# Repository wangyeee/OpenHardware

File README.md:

# OpenHardware
Collections of hardware design related to my drone project.

Brief description for each folders.

| Folder | Description | CAD software |
|---|---|---|
| CurrentMonitor | A simple [ACS758](https://www.allegromicro.com/en/Products/Current-Sensor-ICs/Fifty-To-Two-Hundred-Amp-Integrated-Conductor-Sensor-ICs/ACS758.aspx) breakout board | EAGLE |
| LoRaModem | A board with [Ra-02](http://wiki.ai-thinker.com/_media/lora/docs/c048ps01a1_ra-02_product_specification_v1.1.pdf) LoRa Module and [STM32](https://www.st.com/en/microcontrollers/stm32f103cb.html) MCU | KiCAD |
| OscillatorBreakout | A breakout board for oscillators, supporting three different oscillator packages | KiCAD |
| SimpleFC | Simple yet powerful flight controller for drones, capable of fully autonomous GPS navigation | KiCAD |
| SimpleFCv2 | Version 2 of SimpleFC, with reduced PCB size | KiCAD |
| SimpleFC_G | SimpleFCv2 with integrated GPS receiver | KiCAD |
| MultiRotorHub | A support board in multi-rotor which makes cable management easy | EAGLE |
| PowerModule  | 2s ~ 6s Li-Po BEC with current monitoring |EAGLE  |
| SerialBTBridge | A bridge board between RFM22B telemetry module and HC05 Bluetooth module | EAGLE |
| TinyFC | A tiny flight controller module, supporting board stacking for advanced features | KiCAD |
| ReflowOvenController | A controller board used to convert a commercial oven to PCB reflow oven. | KiCAD |
| AirSensor | A barometer and differential pressure sensor board with UAVCAN support. | KiCAD |
| DIYDummyLoad | A primitive DC dummy load with STM32F103. | EAGLE |
| TinyBEC | 2s ~ 3s / 2A Li-Po BEC, board size 23x18mm. | KiCAD |

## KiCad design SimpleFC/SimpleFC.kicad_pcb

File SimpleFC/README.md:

# SimpleFC
SimpleFC is a simple flight controller for drones.

## Features

- STM32F4 MCU with FPU
- 10DoF IMU (Gyro + Accel + Mag + Baro)
- Onboard UBlox GPS receiver
- DC-DC converter supports up to 6S Li-Po battery with power monitor.
- Two RC input channel with software controlled inverter for S.Bus receivers.
- 8 PWM outputs.
- Onboard TF card slot to record flight data.
- EEPROM to store parameters.
- CAN Bus support.
- USB and SWD available.

## Software
SimpleFC was originally designed to run modified version of [AutoQuad](http://autoquad.org/), the source can be found in my [fork](https://github.com/wangyeee/aq_flight_control) of AutoQuad. In additional, port for [PaparazziUAV](http://wiki.paparazziuav.org/wiki/Main_Page) is in progress. It will make SimpleFC support both fixwing and rotorcraft.

## STM32F4 resource usage
The following table summarizes usage of the MCU, details such as pinout and DMA allocation can be found in the [STM32CubeMX](https://www.st.com/en/development-tools/stm32cubemx.html) design file `SimpleFC.ioc`.

| MCU Peripheral | Usage |
|----|----|
| ADC1 | battery monitor and two analog inputs |
|CAN2 | CAN bus |
| I2C1 | [MAG3110](https://www.nxp.com/docs/en/data-sheet/MAG3110.pdf) magnetometer and EEPROM |
| SDIO | TF card slot |
| SPI1 | [ICM20689](http://www.invensense.com/wp-content/uploads/2017/08/ICM-20689-v2.2-002.pdf) gyroscope/accelerometer and [MS5611](https://www.te.com/commerce/DocumentDelivery/DDEController?Action=showdoc&DocId=Data+Sheet%7FMS5611-01BA03%7FB3%7Fpdf%7FEnglish%7FENG_DS_MS5611-01BA03_B3.pdf%7FCAT-BLPS0036) barometer |
| TIM3, TIM4, TIM12 | 8 channel PWM output |
| UART4, USART2 | RC input, support serial, S.Bus or PPM |
| USART1 | telemetry |
| USART3 | UBlox [NEO-M8N](https://www.u-blox.com/sites/default/files/NEO-M8-FW3_DataSheet_%28UBX-15031086%29.pdf) GPS receiver |
| USB | DFU or CDC telemetry |

## 3D preview and photo
Some 3D models are missing in the KiCAD render, refer to the "real word render" for more details.

Front

Back

Photo

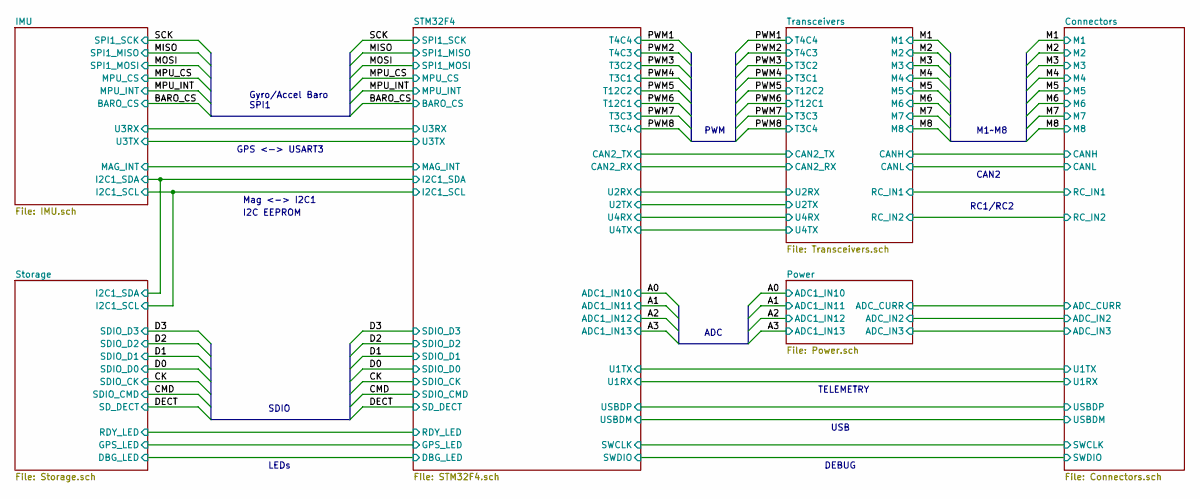
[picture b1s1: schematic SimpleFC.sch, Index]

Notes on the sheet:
SDIO
Gyro/Accel Baro SPI1
Mag <-> I2C1
GPS <-> USART3
PWM
M1~~M8
CAN2
RC1/RC2
DEBUG
I2C EEPROM
LEDs
ADC
USB
TELEMETRY

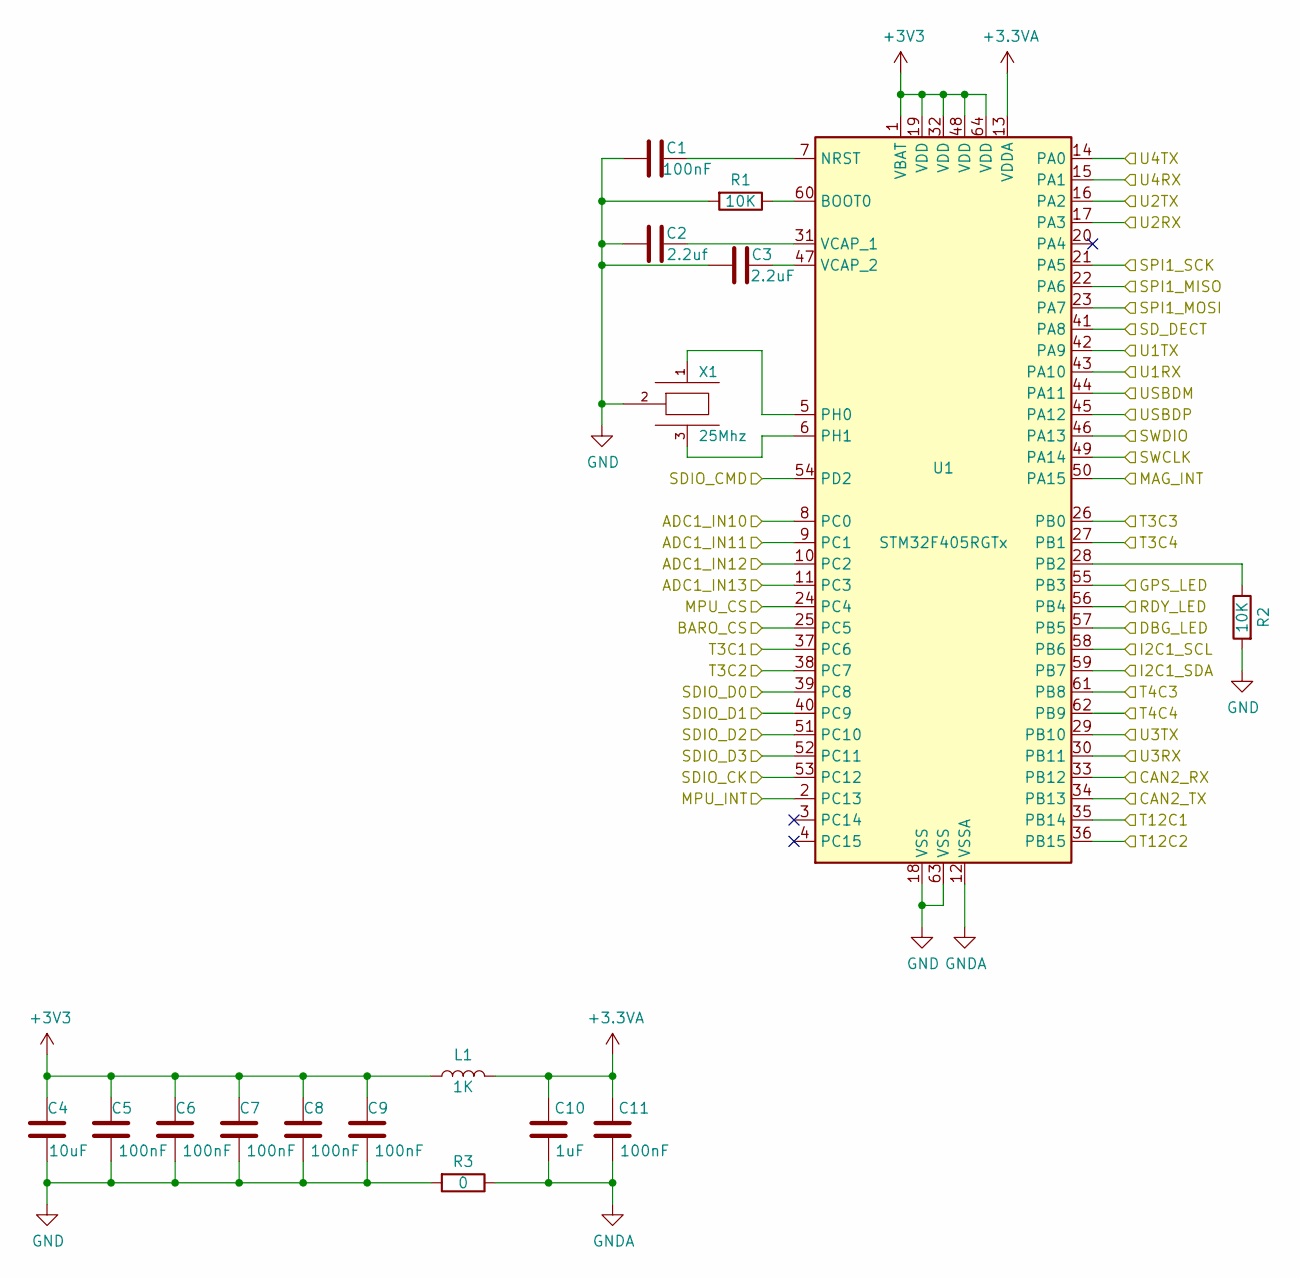
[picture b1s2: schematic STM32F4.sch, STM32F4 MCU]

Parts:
C1, C5, C6, C7, C8, C9, C11: 100nF; C_0603_HandSoldering
C2: 2.2uf; C_0603_HandSoldering
C3: 2.2uF; C_0603_HandSoldering
C4: 10uF; C_0603_HandSoldering
C10: 1uF; C_0603_HandSoldering
L1: 1K; R_0603_HandSoldering
R1, R2: 10K; R_0603_HandSoldering
R3: 0; R_0603_HandSoldering
U1: STM32F405RGTx; LQFP-64_10x10mm_P0.5mm
X1: 25Mhz; CERALOCK-CSTCW

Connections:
+3.3VA: C10.1, C11.1, L1.2, U1.13 (VDDA)
+3V3: C4.1, C5.1, C6.1, C7.1, C8.1, C9.1, L1.1, U1.1 (VBAT), U1.19 (VDD), U1.32 (VDD), U1.48 (VDD), U1.64 (VDD); also elsewhere on the board
/A0: U1.8 (PC0); also elsewhere on the board
/A1: U1.9 (PC1); also elsewhere on the board
/A2: U1.10 (PC2); also elsewhere on the board
/A3: U1.11 (PC3); also elsewhere on the board
/BARO_CS: U1.25 (PC5); also elsewhere on the board
/CK: U1.53 (PC12); also elsewhere on the board
/CMD: U1.54 (PD2); also elsewhere on the board
/Connectors/SWCLK: U1.49 (PA14); also elsewhere on the board
/Connectors/SWDIO: U1.46 (PA13); also elsewhere on the board
/Connectors/U1RX: U1.43 (PA10); also elsewhere on the board
/Connectors/U1TX: U1.42 (PA9); also elsewhere on the board
/Connectors/USBDM: U1.44 (PA11); also elsewhere on the board
/Connectors/USBDP: U1.45 (PA12); also elsewhere on the board
/D0: U1.39 (PC8); also elsewhere on the board
/D1: U1.40 (PC9); also elsewhere on the board
/D2: U1.51 (PC10); also elsewhere on the board
/D3: U1.52 (PC11); also elsewhere on the board
/DECT: U1.41 (PA8); also elsewhere on the board
/IMU/I2C1_SCL: U1.58 (PB6); also elsewhere on the board
/IMU/I2C1_SDA: U1.59 (PB7); also elsewhere on the board
/IMU/MAG_INT: U1.50 (PA15); also elsewhere on the board
/IMU/U3RX: U1.30 (PB11); also elsewhere on the board
/IMU/U3TX: U1.29 (PB10); also elsewhere on the board
/MISO: U1.22 (PA6); also elsewhere on the board
/MOSI: U1.23 (PA7); also elsewhere on the board
/MPU_CS: U1.24 (PC4); also elsewhere on the board
/MPU_INT: U1.2 (PC13); also elsewhere on the board
/PWM1: U1.62 (PB9); also elsewhere on the board
/PWM2: U1.61 (PB8); also elsewhere on the board
/PWM3: U1.38 (PC7); also elsewhere on the board
/PWM4: U1.37 (PC6); also elsewhere on the board
/PWM5: U1.36 (PB15); also elsewhere on the board
/PWM6: U1.35 (PB14); also elsewhere on the board
/PWM7: U1.26 (PB0); also elsewhere on the board
/PWM8: U1.27 (PB1); also elsewhere on the board
/SCK: U1.21 (PA5); also elsewhere on the board
/STM32F4/CAN2_RX: U1.33 (PB12); also elsewhere on the board
/STM32F4/CAN2_TX: U1.34 (PB13); also elsewhere on the board
/STM32F4/DBG_LED: U1.57 (PB5); also elsewhere on the board
/STM32F4/GPS_LED: U1.55 (PB3); also elsewhere on the board
/STM32F4/RDY_LED: U1.56 (PB4); also elsewhere on the board
/STM32F4/U2RX: U1.17 (PA3); also elsewhere on the board
/STM32F4/U2TX: U1.16 (PA2); also elsewhere on the board
/STM32F4/U4RX: U1.15 (PA1); also elsewhere on the board
/STM32F4/U4TX: U1.14 (PA0); also elsewhere on the board
GND: C1.2, C2.2, C3.2, C4.2, C5.2, C6.2, C7.2, C8.2, C9.2, R1.2, R2.2, R3.2, U1.18 (VSS), U1.63 (VSS), X1.2; also elsewhere on the board
GNDA: C10.2, C11.2, R3.1, U1.12 (VSSA); also elsewhere on the board
unnamed: C1.1, U1.7 (NRST)
unnamed: C2.1, U1.31 (VCAP_1)
unnamed: C3.1, U1.47 (VCAP_2)
unnamed: R1.1, U1.60 (BOOT0)
unnamed: R2.1, U1.28 (PB2)
unnamed: U1.5 (PH0), X1.1
unnamed: U1.6 (PH1), X1.3

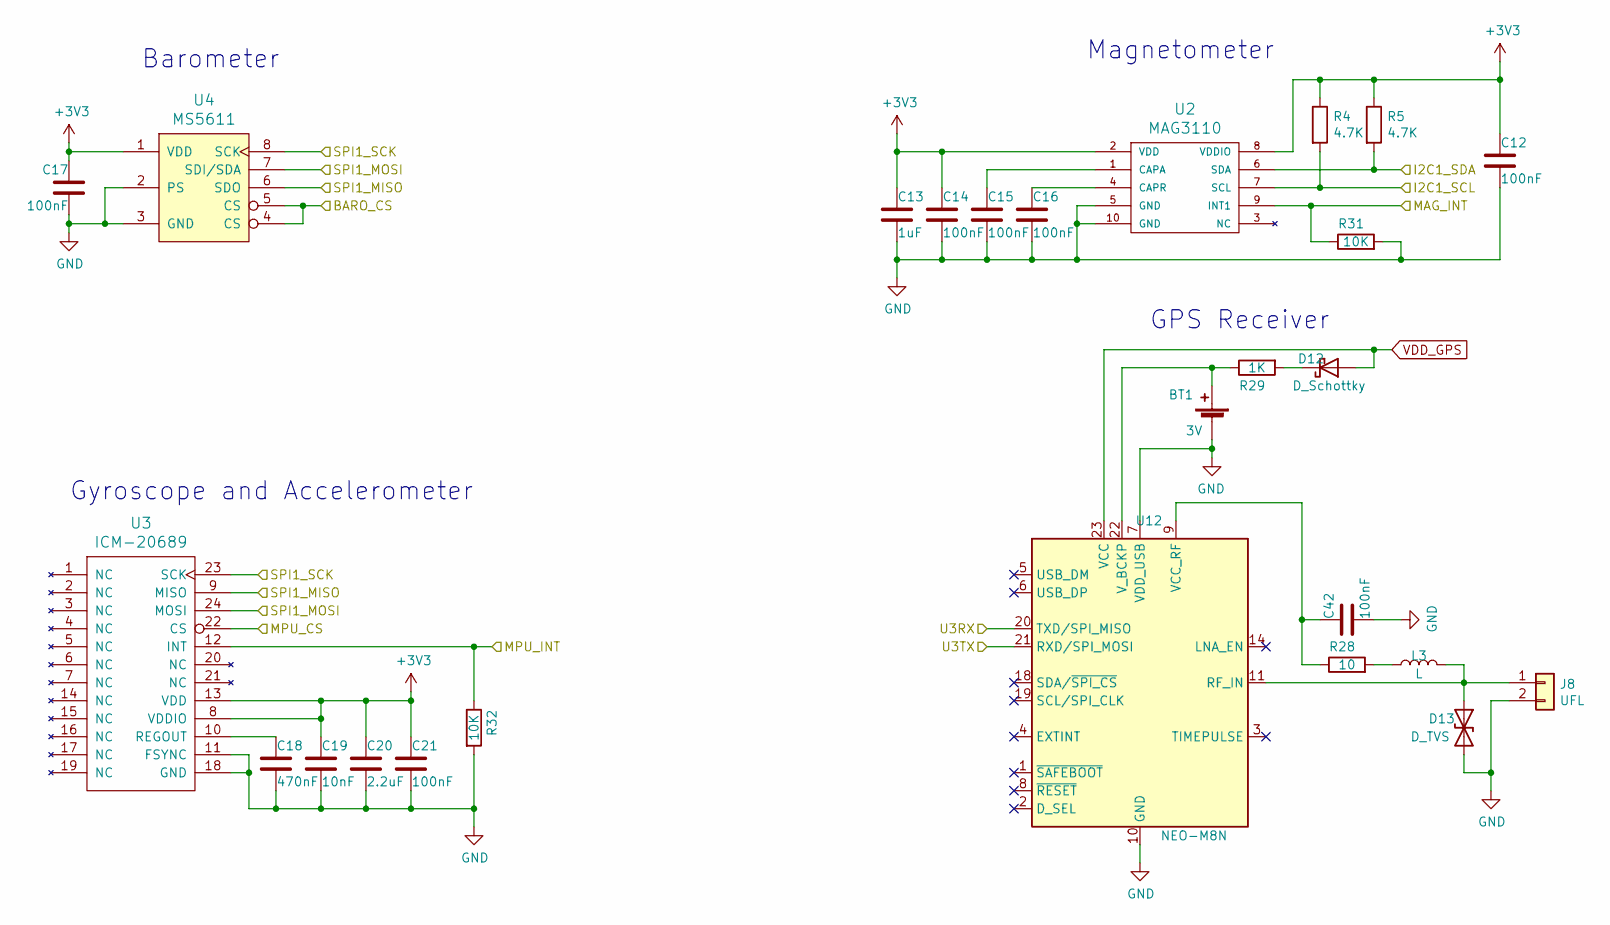
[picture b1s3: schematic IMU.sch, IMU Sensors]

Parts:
BT1: 3V; XH414HG-IV01E
C12, C14, C15, C16, C17, C21, C42: 100nF; C_0603_HandSoldering
C13: 1uF; C_0603_HandSoldering
C18: 470nF; C_0603_HandSoldering
C19: 10nF; C_0603_HandSoldering
C20: 2.2uF; C_0603_HandSoldering
D12: D_Schottky; D_SOD-323_HandSoldering
D13: D_TVS; R_0402
J8: UFL; U.FL_Molex_MCRF_73412-0110_Vertical
L3: L; R_0402
R4, R5: 4.7K; R_0603_HandSoldering
R28: 10; R_0603_HandSoldering
R29: 1K; R_0603_HandSoldering
R31, R32: 10K; R_0603_HandSoldering
U2: MAG3110; DFN-10
U3: ICM-20689; QFN-24_MPU
U4: MS5611; QFN8-5x3
U12: NEO-M8N; UBX-LCC24

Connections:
+3V3: C12.1, C13.1, C14.1, C17.1, C19.1, C20.1, C21.1, R4.1, R5.1, U2.2 (VDD), U2.8 (VDDIO), U3.8 (VDDIO), U3.13 (VDD), U4.1 (VDD); also elsewhere on the board
/BARO_CS: U4.4 (CS), U4.5 (CS); also elsewhere on the board
/IMU/I2C1_SCL: R4.2, U2.7 (SCL); also elsewhere on the board
/IMU/I2C1_SDA: R5.2, U2.6 (SDA); also elsewhere on the board
/IMU/MAG_INT: R31.1, U2.9 (INT1); also elsewhere on the board
/IMU/U3RX: U12.20 (TXD/SPI_MISO); also elsewhere on the board
/IMU/U3TX: U12.21 (RXD/SPI_MOSI); also elsewhere on the board
/MISO: U3.9 (MISO), U4.6 (SDO); also elsewhere on the board
/MOSI: U3.24 (MOSI), U4.7 (SDI/SDA); also elsewhere on the board
/MPU_CS: U3.22 (CS); also elsewhere on the board
/MPU_INT: R32.1, U3.12 (INT); also elsewhere on the board
/SCK: U3.23 (SCK), U4.8 (SCK); also elsewhere on the board
GND: BT1.2 (-), C12.2, C13.2, C14.2, C15.2, C16.2, C17.2, C18.2, C19.2, C20.2, C21.2, C42.2, D13.2 (A2), J8.2, R31.2, R32.2, U2.5 (GND), U2.10 (GND), U3.11 (FSYNC), U3.18 (GND), U4.2 (PS), U4.3 (GND), U12.7 (VDD_USB), U12.10 (GND), U12.12 (GND), U12.13 (GND), U12.24 (GND); also elsewhere on the board
unnamed: BT1.1 (+), R29.1, U12.22 (V_BCKP)
unnamed: C15.1, U2.1 (CAPA)
unnamed: C16.1, U2.4 (CAPR)
unnamed: C18.1, U3.10 (REGOUT)
unnamed: C42.1, R28.1, U12.9 (VCC_RF)
unnamed: D12.1 (K), R29.2
unnamed: D13.1 (A1), J8.1, L3.2, U12.11 (RF_IN)
unnamed: L3.1, R28.2
VDD_GPS: D12.2 (A), U12.23 (VCC); also elsewhere on the board

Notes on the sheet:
Barometer
Magnetometer
Gyroscope and Accelerometer
GPS Receiver

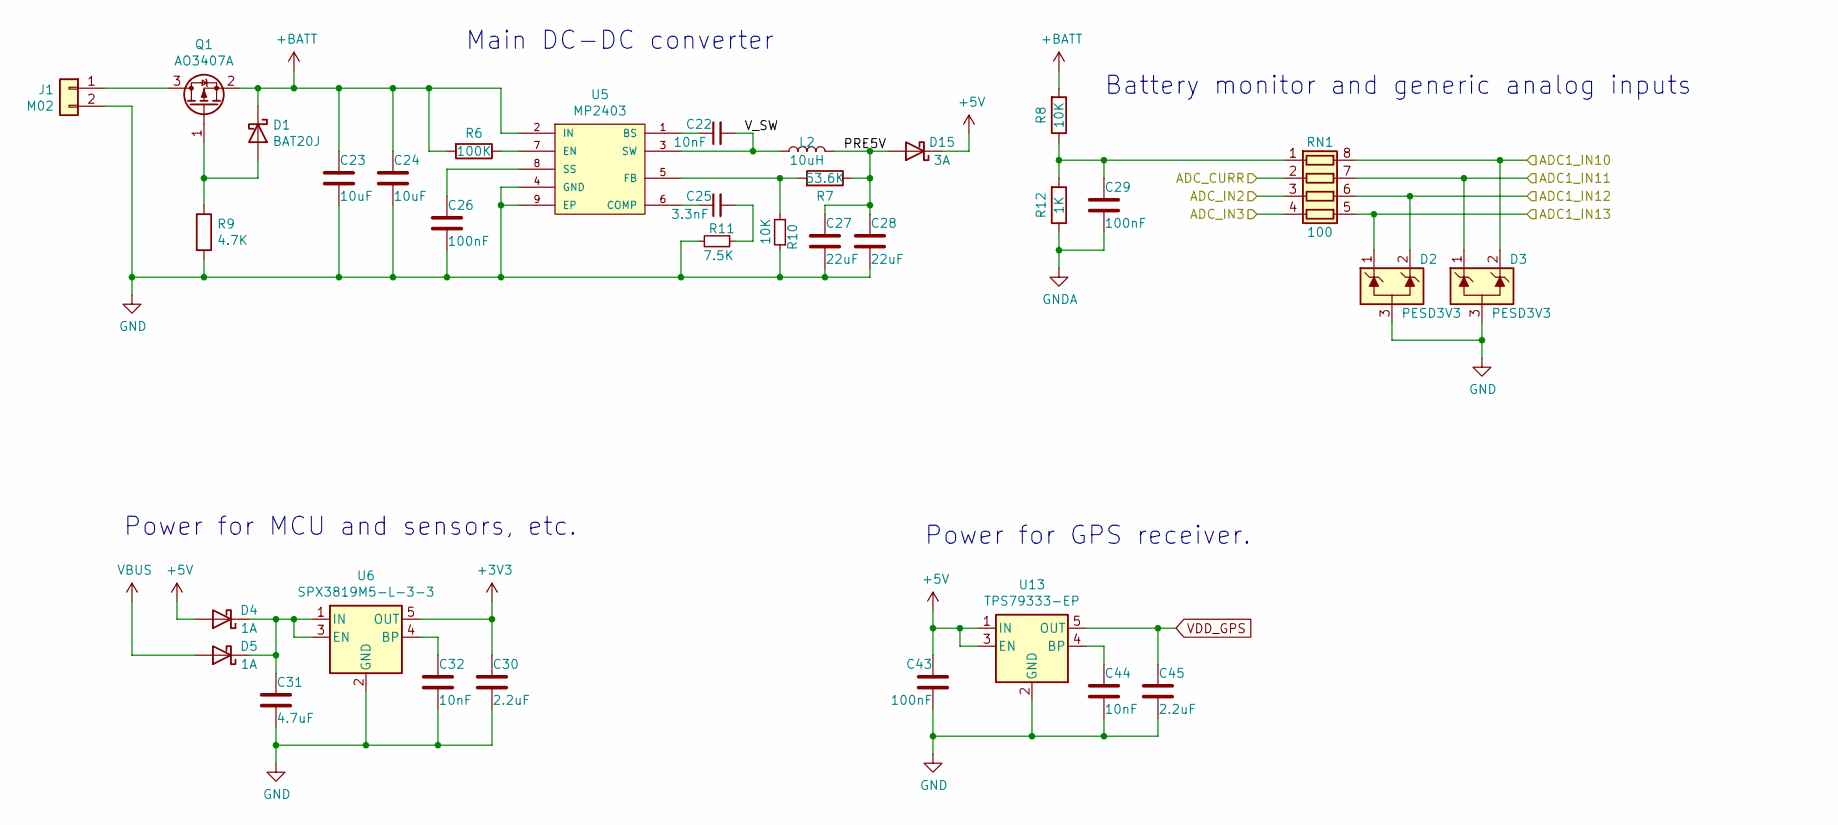
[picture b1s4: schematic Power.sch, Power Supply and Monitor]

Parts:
C22, C32, C44: 10nF; C_0603_HandSoldering
C23, C24: 10uF; C_1206_HandSoldering
C25: 3.3nF; C_0603_HandSoldering
C26, C29, C43: 100nF; C_0603_HandSoldering
C27, C28: 22uF; C_0805_HandSoldering
C30, C45: 2.2uF; C_0603_HandSoldering
C31: 4.7uF; C_0603_HandSoldering
D1: BAT20J; D_SOD-323_HandSoldering
D2, D3: PESD3V3; SOT-23
D4, D5: 1A; D_SOD-123
D15: 3A; D_SMA_Standard
J1: M02
L2: 10uH; SPM6530
Q1: AO3407A; SOT-23
R6: 100K; R_0603_HandSoldering
R7: 53.6K; R_0603_HandSoldering
R8, R10: 10K; R_0603_HandSoldering
R9: 4.7K; R_0603_HandSoldering
R11: 7.5K; R_0603_HandSoldering
R12: 1K; R_0603_HandSoldering
RN1: 100; R_Array_Concave_4x0603
U5: MP2403; SOIC-8-1EP_3.9x4.9mm_Pitch1.27mm
U6: SPX3819M5-L-3-3; SOT-23-5
U13: TPS79333-EP; SOT-23-5

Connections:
+3V3: C30.1, U6.5 (OUT); also elsewhere on the board
+5V: C43.1, D4.2 (A), D15.1 (K), U13.1 (IN), U13.3 (EN); also elsewhere on the board
+BATT: C23.1, C24.1, D1.1 (K), Q1.2 (S), R6.2, R8.2, U5.2 (IN)
/A0: D3.2 (K), RN1.8 (R1.2); also elsewhere on the board
/A1: D3.1 (K), RN1.7 (R2.2); also elsewhere on the board
/A2: D2.2 (K), RN1.6 (R3.2); also elsewhere on the board
/A3: D2.1 (K), RN1.5 (R4.2); also elsewhere on the board
/Connectors/ADC_CURR: RN1.2 (R2.1); also elsewhere on the board
/Connectors/ADC_IN2: RN1.3 (R3.1); also elsewhere on the board
/Connectors/ADC_IN3: RN1.4 (R4.1); also elsewhere on the board
/Power/PRE5V: C27.1, C28.1, D15.2 (A), L2.2, R7.1
/Power/V_SW: C22.2, L2.1, U5.3 (SW)
GND: C23.2, C24.2, C26.2, C27.2, C28.2, C30.2, C31.2, C32.2, C43.2, C44.2, C45.2, D2.3 (A), D3.3 (A), J1.2, R9.2, R10.1, R11.2, U5.4 (GND), U5.9 (EP), U6.2 (GND), U13.2 (GND); also elsewhere on the board
GNDA: C29.2, R12.1; also elsewhere on the board
unnamed: C22.1, U5.1 (BS)
unnamed: C25.1, U5.6 (COMP)
unnamed: C25.2, R11.1
unnamed: C26.1, U5.8 (SS)
unnamed: C29.1, R8.1, R12.2, RN1.1 (R1.1)
unnamed: C31.1, D4.1 (K), D5.1 (K), U6.1 (IN), U6.3 (EN)
unnamed: C32.1, U6.4 (BP)
unnamed: C44.1, U13.4 (BP)
unnamed: D1.2 (A), Q1.1 (G), R9.1
unnamed: J1.1, Q1.3 (D)
unnamed: R6.1, U5.7 (EN)
unnamed: R7.2, R10.2, U5.5 (FB)
VBUS: D5.2 (A); also elsewhere on the board
VDD_GPS: C45.1, U13.5 (OUT); also elsewhere on the board

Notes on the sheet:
Power for MCU and sensors, etc.
Power for GPS receiver.
Main DC-DC converter
Battery monitor and generic analog inputs

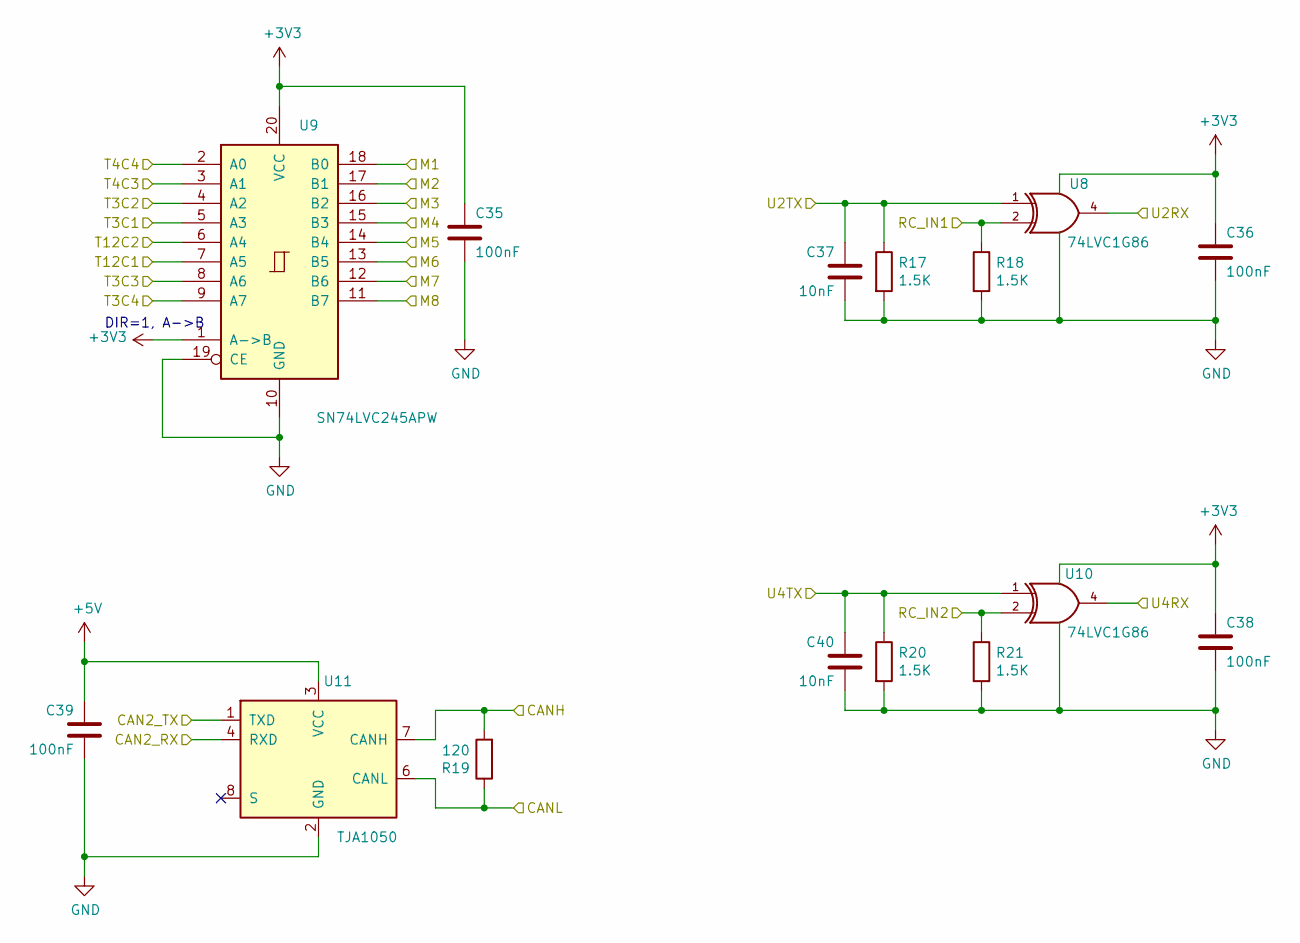
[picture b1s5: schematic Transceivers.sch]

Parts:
C35, C36, C38, C39: 100nF; C_0603_HandSoldering
C37, C40: 10nF; C_0603_HandSoldering
R17, R18, R20, R21: 1.5K; R_0603_HandSoldering
R19: 120; R_0603_HandSoldering
U8, U10: 74LVC1G86; SOT-23-5
U9: SN74LVC245APW; TSSOP-20_4.4x6.5mm_P0.65mm
U11: TJA1050; SOIC-8_3.9x4.9mm_P1.27mm

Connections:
+3V3: C35.1, C36.1, C38.1, U8.5 (VCC), U9.1 (A->B), U9.20 (VCC), U10.5 (VCC); also elsewhere on the board
+5V: C39.1, U11.3 (VCC); also elsewhere on the board
/Connectors/CANH: R19.2, U11.7 (CANH); also elsewhere on the board
/Connectors/CANL: R19.1, U11.6 (CANL); also elsewhere on the board
/Connectors/RC_IN1: R18.1, U8.2; also elsewhere on the board
/Connectors/RC_IN2: R21.1, U10.2; also elsewhere on the board
/M1: U9.18 (B0); also elsewhere on the board
/M2: U9.17 (B1); also elsewhere on the board
/M3: U9.16 (B2); also elsewhere on the board
/M4: U9.15 (B3); also elsewhere on the board
/M5: U9.14 (B4); also elsewhere on the board
/M6: U9.13 (B5); also elsewhere on the board
/M7: U9.12 (B6); also elsewhere on the board
/M8: U9.11 (B7); also elsewhere on the board
/PWM1: U9.2 (A0); also elsewhere on the board
/PWM2: U9.3 (A1); also elsewhere on the board
/PWM3: U9.4 (A2); also elsewhere on the board
/PWM4: U9.5 (A3); also elsewhere on the board
/PWM5: U9.6 (A4); also elsewhere on the board
/PWM6: U9.7 (A5); also elsewhere on the board
/PWM7: U9.8 (A6); also elsewhere on the board
/PWM8: U9.9 (A7); also elsewhere on the board
/STM32F4/CAN2_RX: U11.4 (RXD); also elsewhere on the board
/STM32F4/CAN2_TX: U11.1 (TXD); also elsewhere on the board
/STM32F4/U2RX: U8.4; also elsewhere on the board
/STM32F4/U2TX: C37.1, R17.1, U8.1; also elsewhere on the board
/STM32F4/U4RX: U10.4; also elsewhere on the board
/STM32F4/U4TX: C40.1, R20.1, U10.1; also elsewhere on the board
GND: C35.2, C36.2, C37.2, C38.2, C39.2, C40.2, R17.2, R18.2, R20.2, R21.2, U8.3 (GND), U9.10 (GND), U9.19 (CE), U10.3 (GND), U11.2 (GND); also elsewhere on the board

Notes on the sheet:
DIR=1, A->B

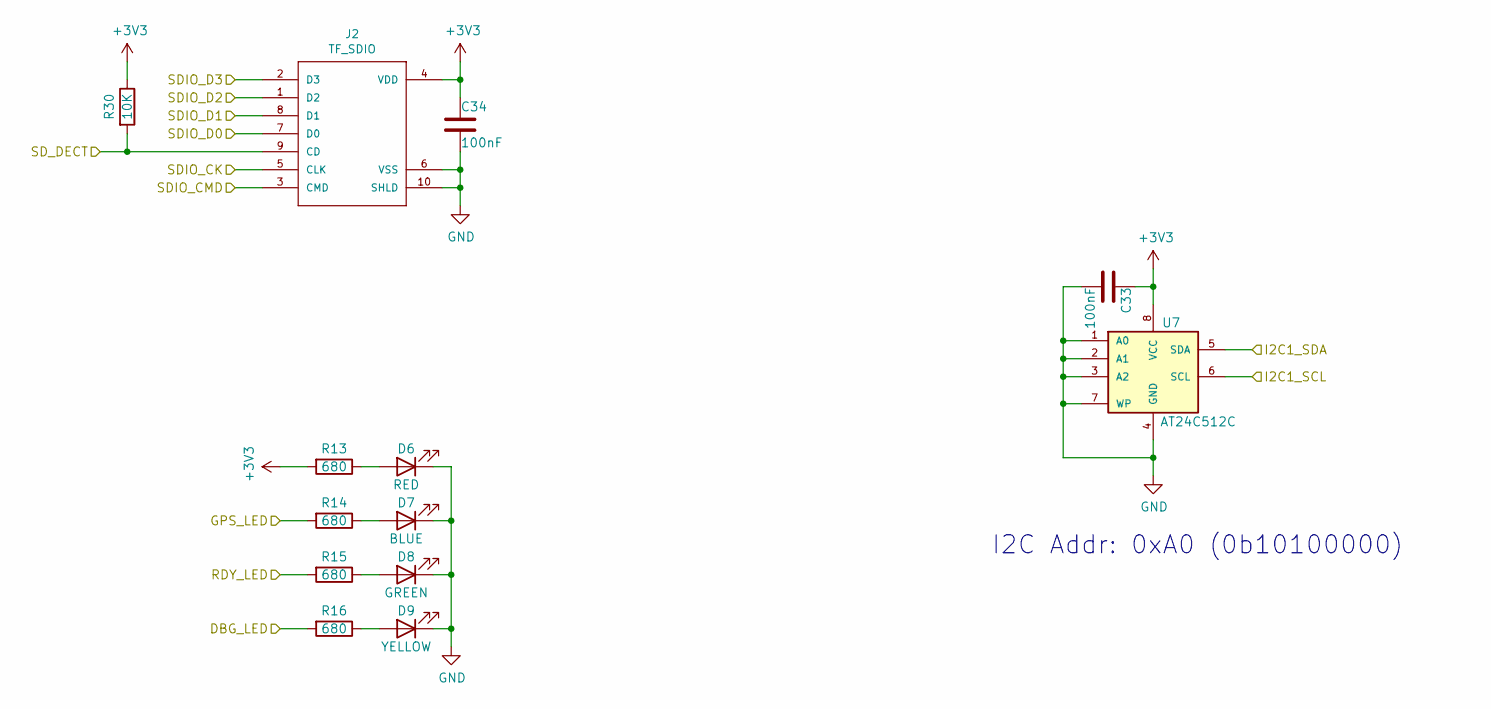
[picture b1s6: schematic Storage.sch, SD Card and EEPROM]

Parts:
C33, C34: 100nF; C_0603_HandSoldering
D6: RED; LED_0603_1608Metric_Pad0.67x1.00mm_HandSolder
D7: BLUE; LED_0603_1608Metric_Pad0.67x1.00mm_HandSolder
D8: GREEN; LED_0603_1608Metric_Pad0.67x1.00mm_HandSolder
D9: YELLOW; LED_0603_1608Metric_Pad0.67x1.00mm_HandSolder
J2: TF_SDIO; TFCARD
R13, R14, R15, R16: 680; R_0603_HandSoldering
R30: 10K; R_0603_HandSoldering
U7: AT24C512C; SOIC-8_3.9x4.9mm_Pitch1.27mm

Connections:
+3V3: C33.1, C34.1, J2.4 (VDD), R13.2, R30.1, U7.8 (VCC); also elsewhere on the board
/CK: J2.5 (CLK); also elsewhere on the board
/CMD: J2.3 (CMD); also elsewhere on the board
/D0: J2.7 (D0); also elsewhere on the board
/D1: J2.8 (D1); also elsewhere on the board
/D2: J2.1 (D2); also elsewhere on the board
/D3: J2.2 (D3); also elsewhere on the board
/DECT: J2.9 (CD), R30.2; also elsewhere on the board
/IMU/I2C1_SCL: U7.6 (SCL); also elsewhere on the board
/IMU/I2C1_SDA: U7.5 (SDA); also elsewhere on the board
/STM32F4/DBG_LED: R16.2; also elsewhere on the board
/STM32F4/GPS_LED: R14.2; also elsewhere on the board
/STM32F4/RDY_LED: R15.2; also elsewhere on the board
GND: C33.2, C34.2, D6.1 (K), D7.1 (K), D8.1 (K), D9.1 (K), J2.6 (VSS), J2.10 (SHLD), J2.11 (SHLD), J2.12 (SHLD), J2.13 (SHLD), U7.1 (A0), U7.2 (A1), U7.3 (A2), U7.4 (GND), U7.7 (WP); also elsewhere on the board
unnamed: D6.2 (A), R13.1
unnamed: D7.2 (A), R14.1
unnamed: D8.2 (A), R15.1
unnamed: D9.2 (A), R16.1

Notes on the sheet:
I2C Addr: 0xA0 (0b10100000)

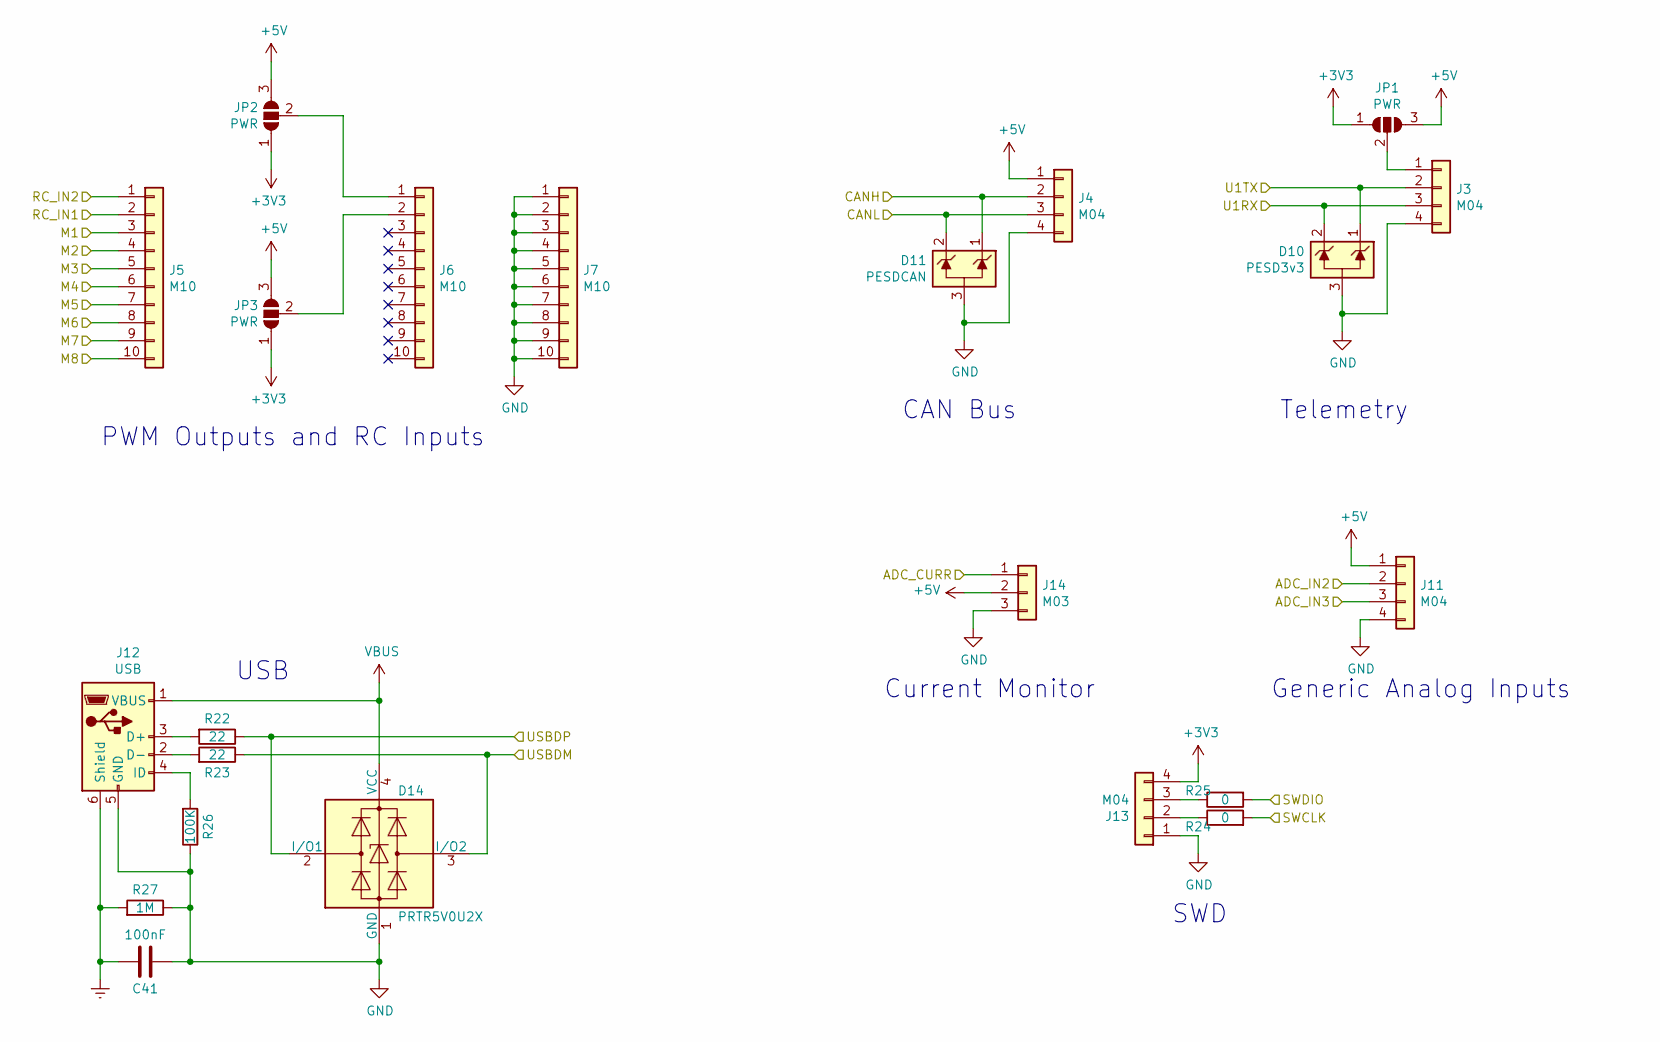
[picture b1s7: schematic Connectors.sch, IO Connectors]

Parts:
C41: 100nF; C_0603_HandSoldering
D10: PESD3v3; SOT-23
D11: PESDCAN; SOT-23
D14: PRTR5V0U2X; SOT143B
J3, J4, J11: M04
J5, J6, J7: M10
J12: USB; USB-AB-MICRO
J13: M04; M04-1.25T
J14: M03
JP1, JP2, JP3: PWR; JUMPER_DUAL_SMALL
R22, R23: 22; R_0603_HandSoldering
R24, R25: 0; R_0402
R26: 100K; R_0603_HandSoldering
R27: 1M; R_0603_HandSoldering

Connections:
+3V3: J13.4, JP1.1 (A), JP2.1 (A), JP3.1 (A); also elsewhere on the board
+5V: J4.1, J11.1, J14.2, JP1.3 (B), JP2.3 (B), JP3.3 (B); also elsewhere on the board
/Connectors/ADC_CURR: J14.1; also elsewhere on the board
/Connectors/ADC_IN2: J11.2; also elsewhere on the board
/Connectors/ADC_IN3: J11.3; also elsewhere on the board
/Connectors/CANH: D11.1 (K), J4.2; also elsewhere on the board
/Connectors/CANL: D11.2 (K), J4.3; also elsewhere on the board
/Connectors/RC_IN1: J5.2; also elsewhere on the board
/Connectors/RC_IN2: J5.1; also elsewhere on the board
/Connectors/SWCLK: R24.2; also elsewhere on the board
/Connectors/SWDIO: R25.2; also elsewhere on the board
/Connectors/U1RX: D10.2 (K), J3.3; also elsewhere on the board
/Connectors/U1TX: D10.1 (K), J3.2; also elsewhere on the board
/Connectors/USBDM: D14.3 (I/O2), R23.1; also elsewhere on the board
/Connectors/USBDP: D14.2 (I/O1), R22.1; also elsewhere on the board
/M1: J5.3; also elsewhere on the board
/M2: J5.4; also elsewhere on the board
/M3: J5.5; also elsewhere on the board
/M4: J5.6; also elsewhere on the board
/M5: J5.7; also elsewhere on the board
/M6: J5.8; also elsewhere on the board
/M7: J5.9; also elsewhere on the board
/M8: J5.10; also elsewhere on the board
Earth: C41.1, J12.6 (Shield), R27.2
GND: C41.2, D10.3 (A), D11.3 (A), D14.1 (GND), J3.4, J4.4, J7.1, J7.2, J7.3, J7.4, J7.5, J7.6, J7.7, J7.8, J7.9, J7.10, J11.4, J12.5 (GND), J13.1, J14.3, R26.1, R27.1; also elsewhere on the board
unnamed: J3.1, JP1.2 (C)
unnamed: J6.1, JP2.2 (C)
unnamed: J6.2, JP3.2 (C)
unnamed: J12.2 (D-), R23.2
unnamed: J12.3 (D+), R22.2
unnamed: J12.4 (ID), R26.2
unnamed: J13.2, R24.1
unnamed: J13.3, R25.1
VBUS: D14.4 (VCC), J12.1 (VBUS); also elsewhere on the board

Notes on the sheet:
USB
PWM Outputs and RC Inputs
CAN Bus
Telemetry
Current Monitor
Generic Analog Inputs
SWD

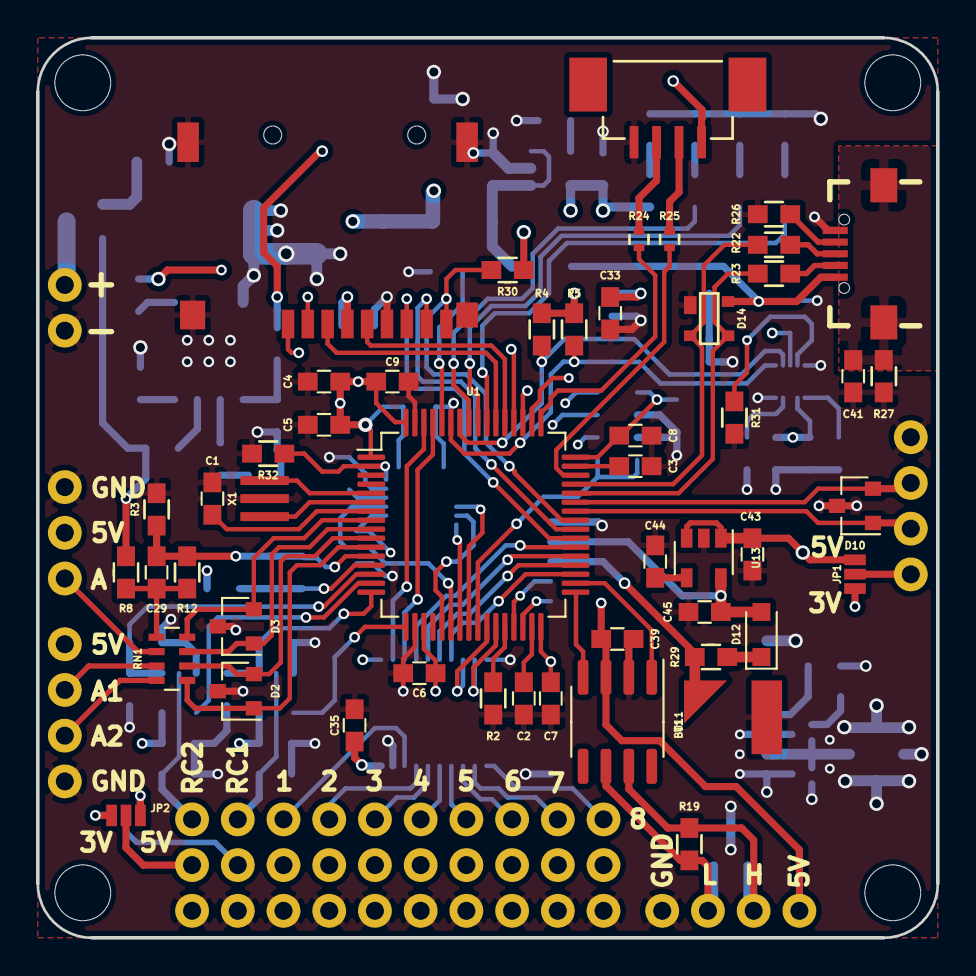
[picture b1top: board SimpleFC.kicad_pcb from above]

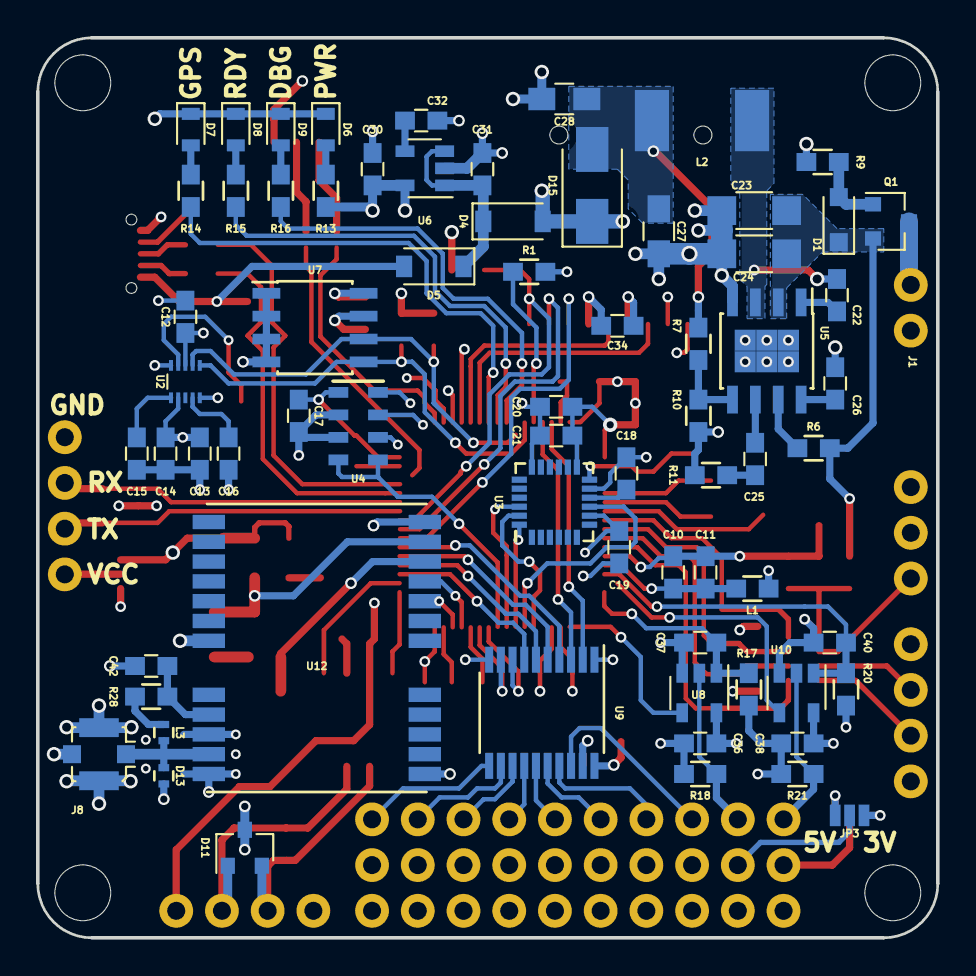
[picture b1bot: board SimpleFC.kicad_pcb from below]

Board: 4 copper layers, 50.0 x 50.0 mm, 127 parts (70 on the bottom side), 110 nets.
